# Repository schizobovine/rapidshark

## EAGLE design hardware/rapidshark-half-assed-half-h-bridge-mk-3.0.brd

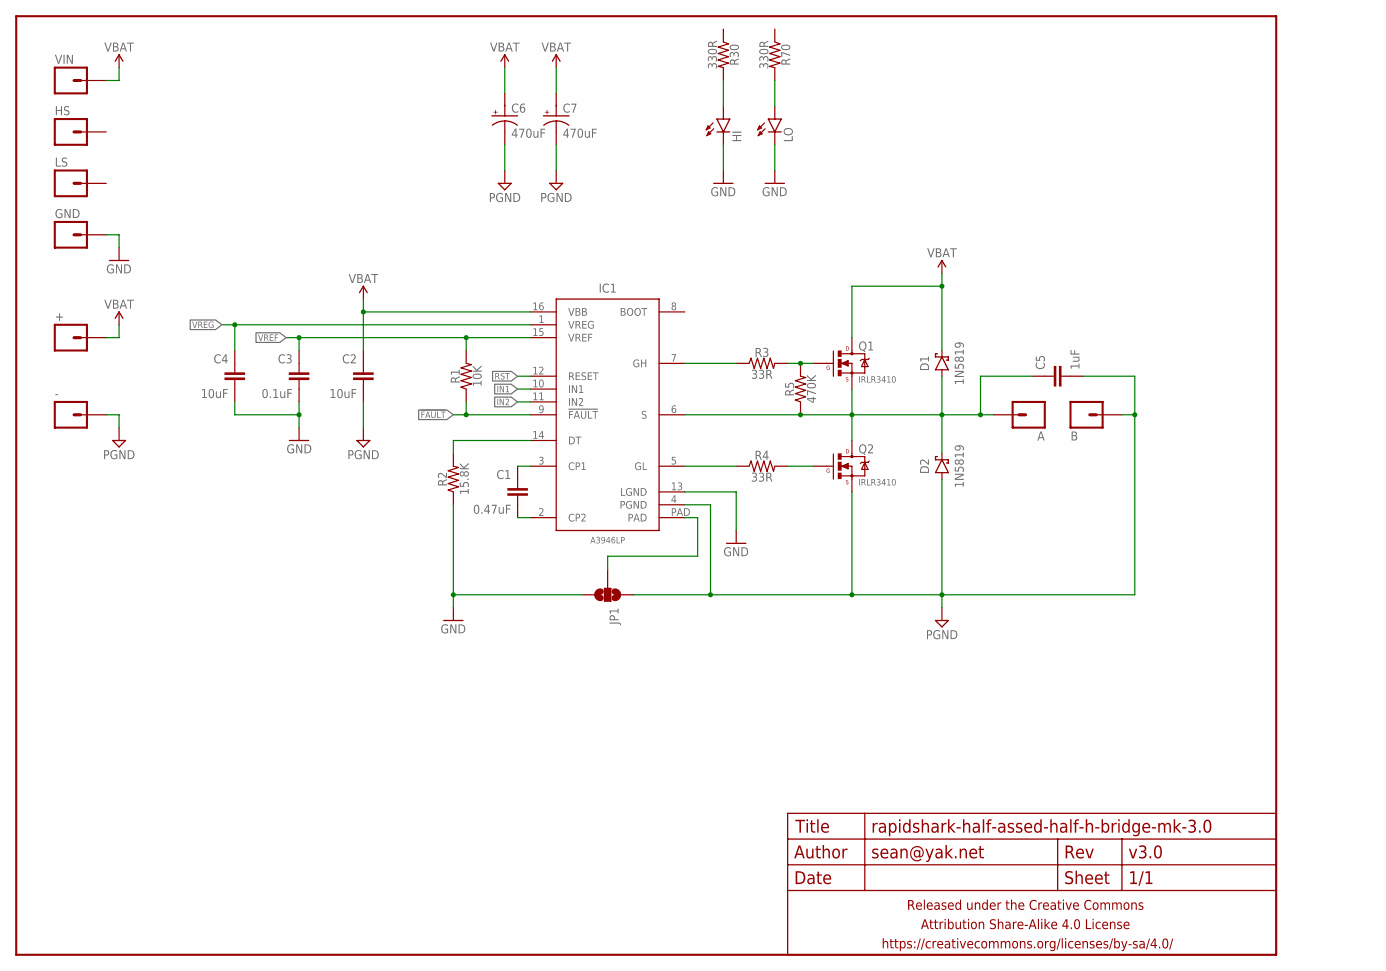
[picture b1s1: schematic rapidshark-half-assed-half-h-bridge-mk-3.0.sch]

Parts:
+: M01PTH-1.9MM; 1X01-1.9MM-CIR
-: M01PTH-1.9MM; 1X01-1.9MM-CIR
A: M01PTH-1.9MM; 1X01-1.9MM-CIR
B: M01PTH-1.9MM; 1X01-1.9MM-CIR
C1: 0.47uF; C0603-TIGHTER
C2, C4: 10uF; C0805-TIGHTER
C3: 0.1uF; C0603-TIGHTER
C5: 1uF; C0603-TIGHTER
C6, C7: 470uF; E5-10,5
D1, D2: 1N5819; SMA-DIODE-SCHOTTKY
FRAME1: FRAME-LETTERNO_PACKAGE; DUMMY
GND: M01PTH; 1X01
HI: LED0603-TIGHT; LED-0603-TIGHT
HS: M01PTH; 1X01
IC1: A3946LP; TSSOP-16-PAD
JP1: JUMPER-PAD-3-NOFULL_BOX_SILK; PAD-JUMPER-3-NO_YES_SILK_FULL_BOX
LO: LED0603-TIGHT; LED-0603-TIGHT
LS: M01PTH; 1X01
Q1, Q2: IRLR3410; DPAK
R1: 10K; R0603-TIGHTER
R2: 15.8K; R0603-TIGHTER
R3, R4: 33R; R0603-TIGHTER
R5: 470K; R0603-TIGHTER
R30, R70: 330R; R0603-TIGHTER
VIN: M01PTH; 1X01

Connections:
!FAULT: IC1.9 (!FAULT), R1.1
A: A.P$1, C5.1, D1.A, D2.C, IC1.6 (S), Q1.3 (S), Q2.4 (D), R5.1
GND: C3.2, C4.2, GND.1, HI.C, IC1.13 (LGND), JP1.3, LO.C, R2.1
IN1: IC1.10 (IN1)
IN2: IC1.11 (IN2)
unnamed: Q2.1 (G), R4.2
unnamed: C1.1, IC1.3 (CP1)
unnamed: LO.A, R70.2
unnamed: HI.A, R30.2
unnamed: Q1.1 (G), R3.2, R5.2
unnamed: C1.2, IC1.2 (CP2)
unnamed: IC1.14 (DT), R2.2
unnamed: IC1.PAD, JP1.2
unnamed: IC1.5 (GL), R4.1
unnamed: IC1.7 (GH), R3.1
PGND: -.P$1, B.P$1, C2.2, C5.2, C6.-, C7.-, D2.A, IC1.4 (PGND), JP1.1, Q2.3 (S)
RST: IC1.12 (RESET)
VBAT: +.P$1, C2.1, C6.+, C7.+, D1.C, IC1.16 (VBB), Q1.4 (D), VIN.1
VREF: C3.1, IC1.15 (VREF), R1.2
VREG: C4.1, IC1.1 (VREG)

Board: 2 copper layers, 34 parts (5 on the bottom side), 17 nets, no tracks yet.

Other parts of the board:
U$1: COW
U$2: CC-BY-SA-4.0-NO-URL
U$3: OSHWLOGO_5MM

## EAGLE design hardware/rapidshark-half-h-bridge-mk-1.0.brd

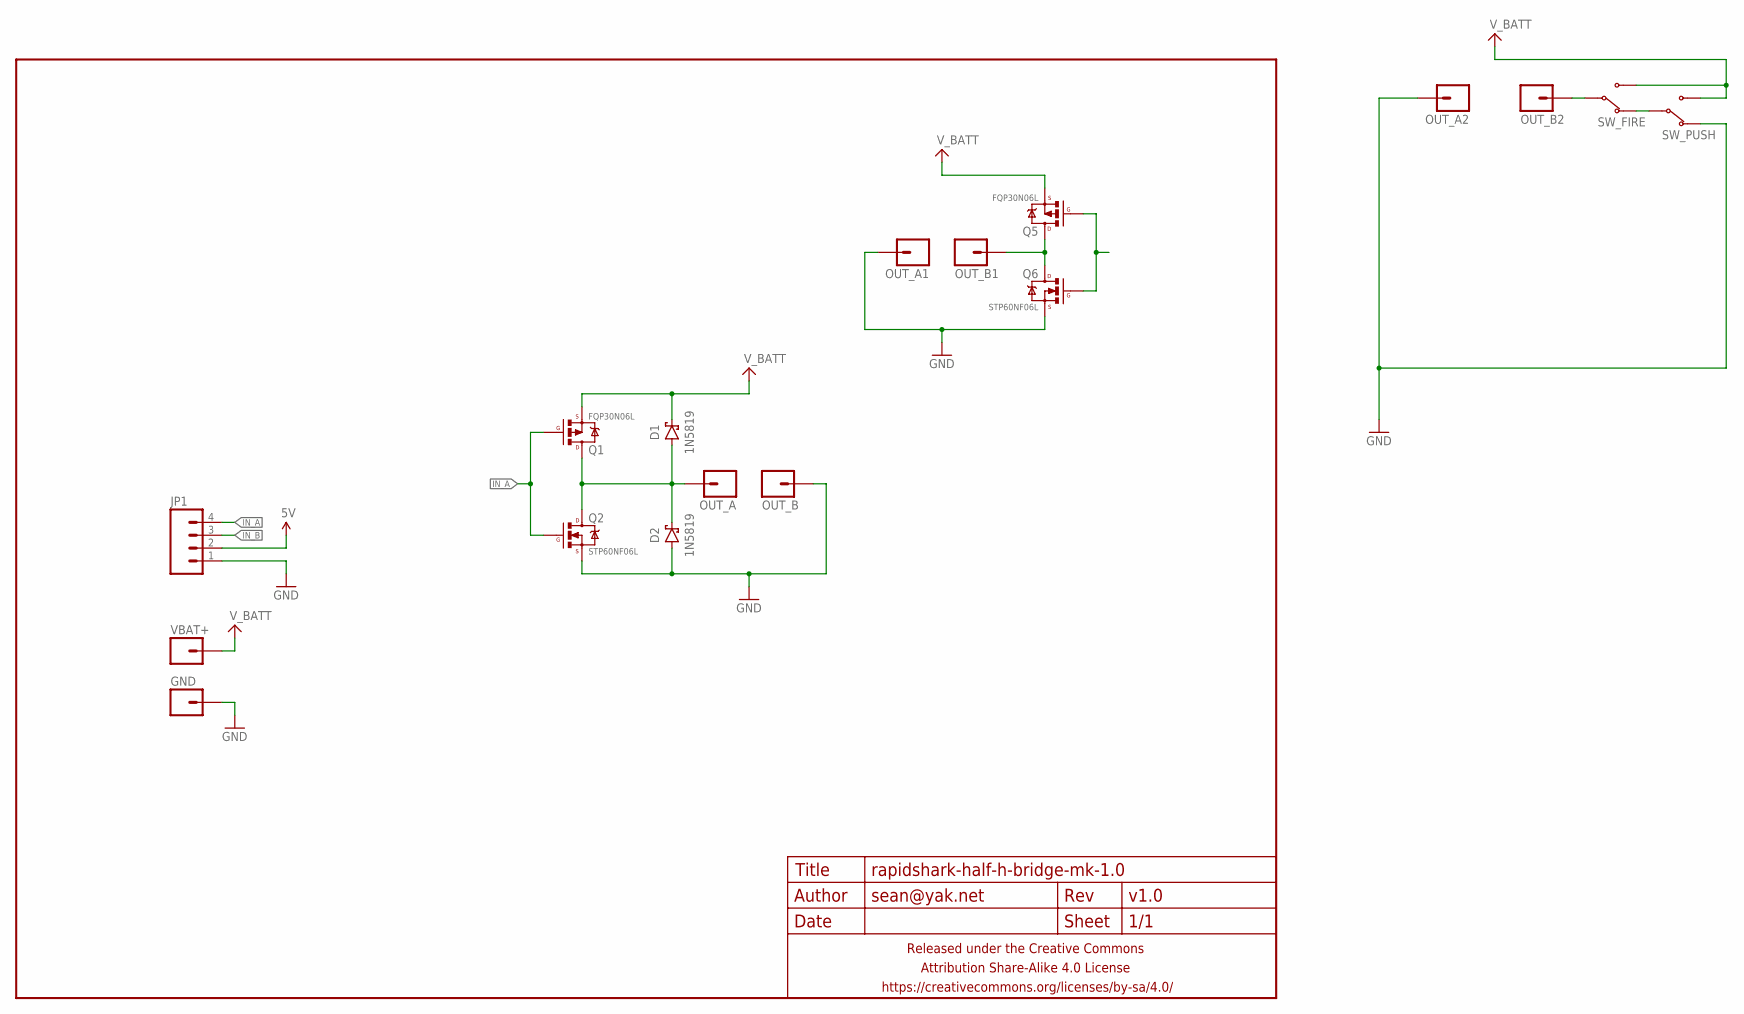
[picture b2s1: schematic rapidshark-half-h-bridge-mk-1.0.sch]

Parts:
D1, D2: 1N5819; DIODE-SCHOTTKY-10.16MM
FRAME1: FRAME-LETTERNO_PACKAGE; DUMMY
GND: M0112AWG; 1X01-12AWG
JP1: M04PTH; 1X04-PTH-VERT
OUT_A, OUT_A1, OUT_A2: M0112AWG; 1X01-12AWG
OUT_B, OUT_B1, OUT_B2: M0112AWG; 1X01-12AWG
Q1, Q5: FQP30N06L; TO220-THERMPAD
Q2, Q6: STP60NF06L; TO220-THERMPAD
SW_FIRE: SWITCH-SPDTPTH-VERT-2.54MM; SWITCH-SPDT
SW_PUSH: SWITCH-SPDTPTH-VERT-2.54MM; SWITCH-SPDT
VBAT+: M0112AWG; 1X01-12AWG

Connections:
5V: JP1.2
A: D1.A, D2.C, OUT_A.1, Q1.2@1 (D), Q1.2@2 (D), Q2.2@1 (D), Q2.2@2 (D)
GND: D2.A, GND.1, JP1.1, OUT_A1.1, OUT_A2.1, OUT_B.1, Q2.3 (S), Q6.3 (S), SW_PUSH.1 (NC)
IN_A: JP1.4, Q1.1 (G), Q2.1 (G)
IN_B: JP1.3
unnamed: OUT_B1.1, Q5.2@1 (D), Q5.2@2 (D), Q6.2@1 (D), Q6.2@2 (D)
unnamed: SW_FIRE.1 (NC), SW_PUSH.2 (COM)
unnamed: OUT_B2.1, SW_FIRE.2 (COM)
unnamed: Q5.1 (G), Q6.1 (G)
V_BATT: D1.C, Q1.3 (S), Q5.3 (S), SW_FIRE.3 (NO), SW_PUSH.3 (NO), VBAT+.1

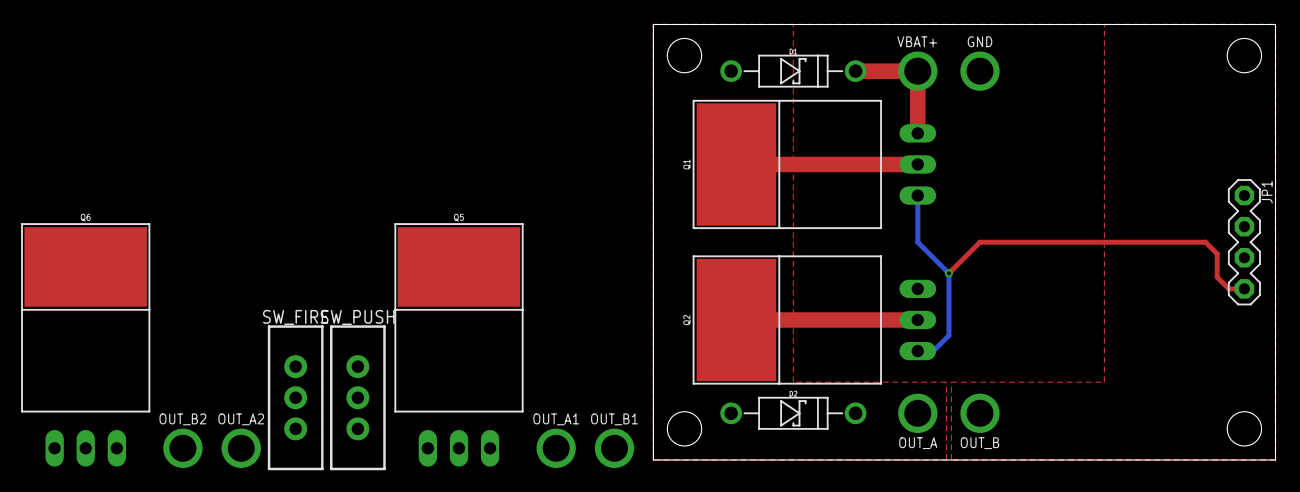
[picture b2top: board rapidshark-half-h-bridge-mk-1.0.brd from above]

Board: 2 copper layers, 50.8 x 35.6 mm, 18 parts (1 on the bottom side), 8 nets.

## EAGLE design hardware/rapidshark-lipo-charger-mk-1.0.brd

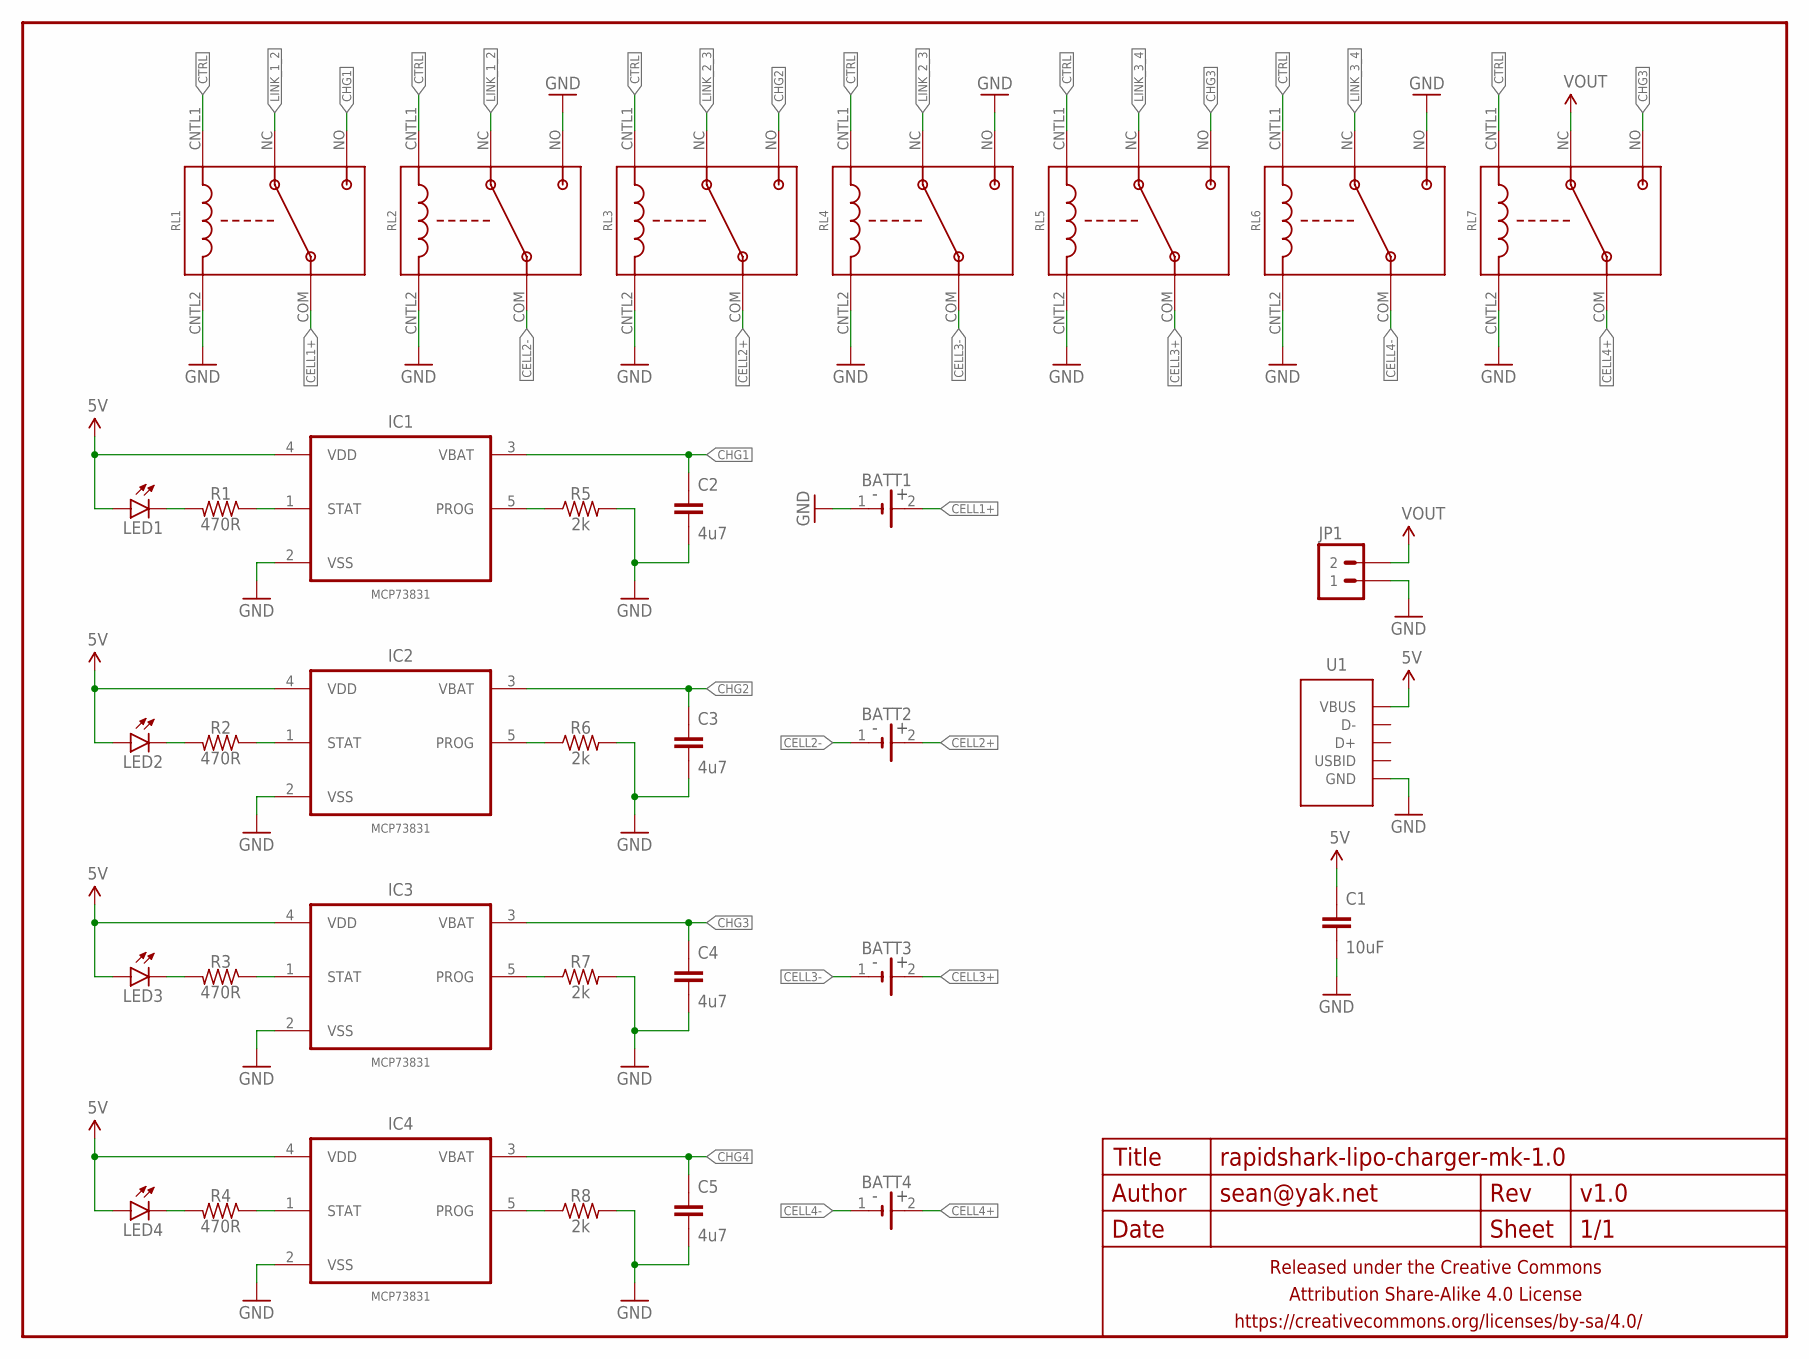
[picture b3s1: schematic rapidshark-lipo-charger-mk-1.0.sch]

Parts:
BATT1, BATT2, BATT3, BATT4: LIPO1S_3.7V_EXT0.1IN_PTH; 1X02-CENTER-R+
C1: 10uF; C0805
C2, C3, C4, C5: 4u7; C0805
FRAME1: FRAME-LETTERNO_PACKAGE; DUMMY
IC1, IC2, IC3, IC4: MCP73831; SOT95P280X145-5N
JP1: M025MM; SCREWTERMINAL-5MM-2
LED1, LED2, LED3, LED4: LED0805; LED-0805
R1, R2, R3, R4: 470R; R0805
R5, R6, R7, R8: 2k; R0805
RL1, RL2, RL3, RL4, RL5, RL6, RL7: RELAY-SPDTMC25131; RELAY-SPDT-MC25131
U1: USB-ABFCI-10103594-USB-MICRO-B-LESS; FCI-10103594-USB-MICRO-B-LESS

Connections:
5V: C1.1, IC1.4 (VDD), IC2.4 (VDD), IC3.4 (VDD), IC4.4 (VDD), LED1.A, LED2.A, LED3.A, LED4.A, U1.1 (VBUS)
CELL1+: BATT1.2 (+), RL1.COM
CELL2+: BATT2.2 (+), RL3.COM
CELL2-: BATT2.1 (-), RL2.COM
CELL3+: BATT3.2 (+), RL5.COM
CELL3-: BATT3.1 (-), RL4.COM
CELL4+: BATT4.2 (+), RL7.COM
CELL4-: BATT4.1 (-), RL6.COM
CHG1: C2.1, IC1.3 (VBAT), RL1.NO
CHG2: C3.1, IC2.3 (VBAT), RL3.NO
CHG3: C4.1, IC3.3 (VBAT), RL5.NO, RL7.NO
CHG4: C5.1, IC4.3 (VBAT)
CTRL: RL1.CNTL1, RL2.CNTL1, RL3.CNTL1, RL4.CNTL1, RL5.CNTL1, RL6.CNTL1, RL7.CNTL1
GND: BATT1.1 (-), C1.2, C2.2, C3.2, C4.2, C5.2, IC1.2 (VSS), IC2.2 (VSS), IC3.2 (VSS), IC4.2 (VSS), JP1.1, R5.2, R6.2, R7.2, R8.2, RL1.CNTL2, RL2.CNTL2, RL2.NO, RL3.CNTL2, RL4.CNTL2, RL4.NO, RL5.CNTL2, RL6.CNTL2, RL6.NO, RL7.CNTL2, U1.5 (GND)
LINK_1_2: RL1.NC, RL2.NC
LINK_2_3: RL3.NC, RL4.NC
LINK_3_4: RL5.NC, RL6.NC
unnamed: LED1.C, R1.2
unnamed: IC1.1 (STAT), R1.1
unnamed: LED2.C, R2.2
unnamed: LED3.C, R3.2
unnamed: LED4.C, R4.2
unnamed: IC2.1 (STAT), R2.1
unnamed: IC3.1 (STAT), R3.1
unnamed: IC4.1 (STAT), R4.1
unnamed: IC1.5 (PROG), R5.1
unnamed: IC2.5 (PROG), R6.1
unnamed: IC3.5 (PROG), R7.1
unnamed: IC4.5 (PROG), R8.1
VOUT: JP1.2, RL7.NC

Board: 2 copper layers, 35 parts (0 on the bottom side), 30 nets, no tracks yet.

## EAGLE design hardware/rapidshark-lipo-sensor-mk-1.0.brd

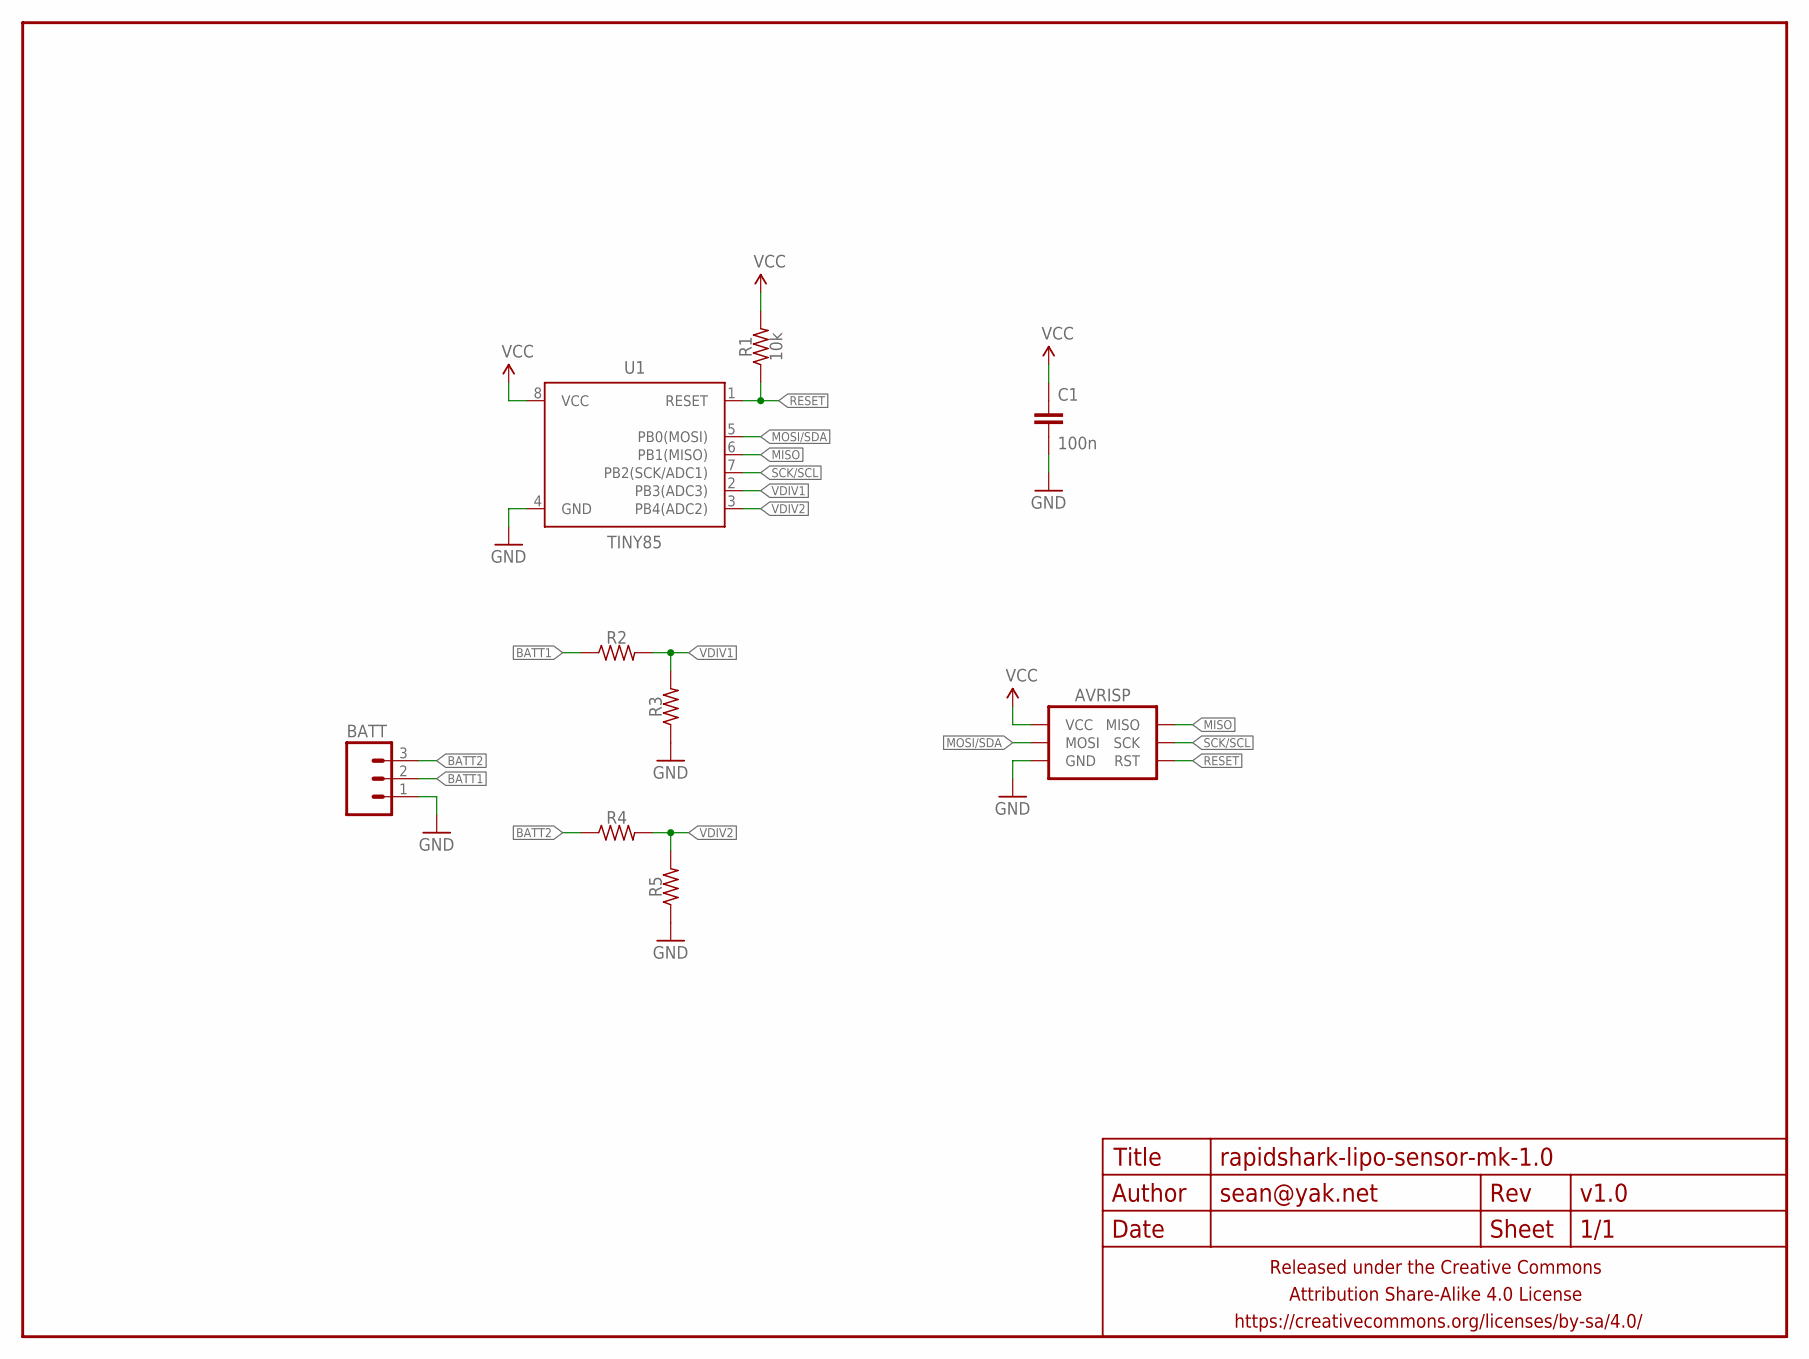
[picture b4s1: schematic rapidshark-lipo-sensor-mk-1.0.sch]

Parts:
AVRISP: AVR_SPI_PRG_6PTH_INLINE_I2C; AVR_ISP_INLINE_PTH_I2C
BATT: M03PTH-CENTERED; 1X03-CENTERED
C1: 100n; C025-024X044
FRAME1: FRAME-LETTERNO_PACKAGE; DUMMY
R1: 10k; RESISTOR-AXIAL-PTH-7.62MM
R2, R3, R4, R5: RESISTORPTH-AXIAL-7.62MM; RESISTOR-AXIAL-PTH-7.62MM
U1: TINY85; DIP08

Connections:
BATT1: BATT.2, R2.P$1 (1)
BATT2: BATT.3, R4.P$1 (1)
GND: AVRISP.GND, BATT.1, C1.2, R3.P$1 (1), R5.P$1 (1), U1.4 (GND)
MISO: AVRISP.MISO, U1.6 (PB1(MISO))
MOSI/SDA: AVRISP.MOSI, U1.5 (PB0(MOSI))
RESET: AVRISP.RESET (RST), R1.P$1 (1), U1.1 (RESET)
SCK/SCL: AVRISP.SCK, U1.7 (PB2(SCK/ADC1))
VCC: AVRISP.VCC, C1.1, R1.P$2 (2), U1.8 (VCC)
VDIV1: R2.P$2 (2), R3.P$2 (2), U1.2 (PB3(ADC3))
VDIV2: R4.P$2 (2), R5.P$2 (2), U1.3 (PB4(ADC2))

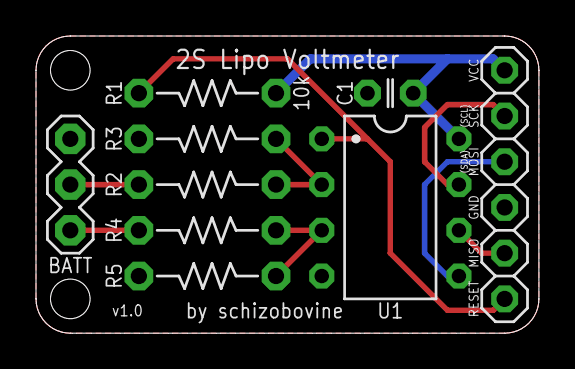
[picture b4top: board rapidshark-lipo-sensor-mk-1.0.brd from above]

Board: 2 copper layers, 27.9 x 16.5 mm, 10 parts (0 on the bottom side), 10 nets.

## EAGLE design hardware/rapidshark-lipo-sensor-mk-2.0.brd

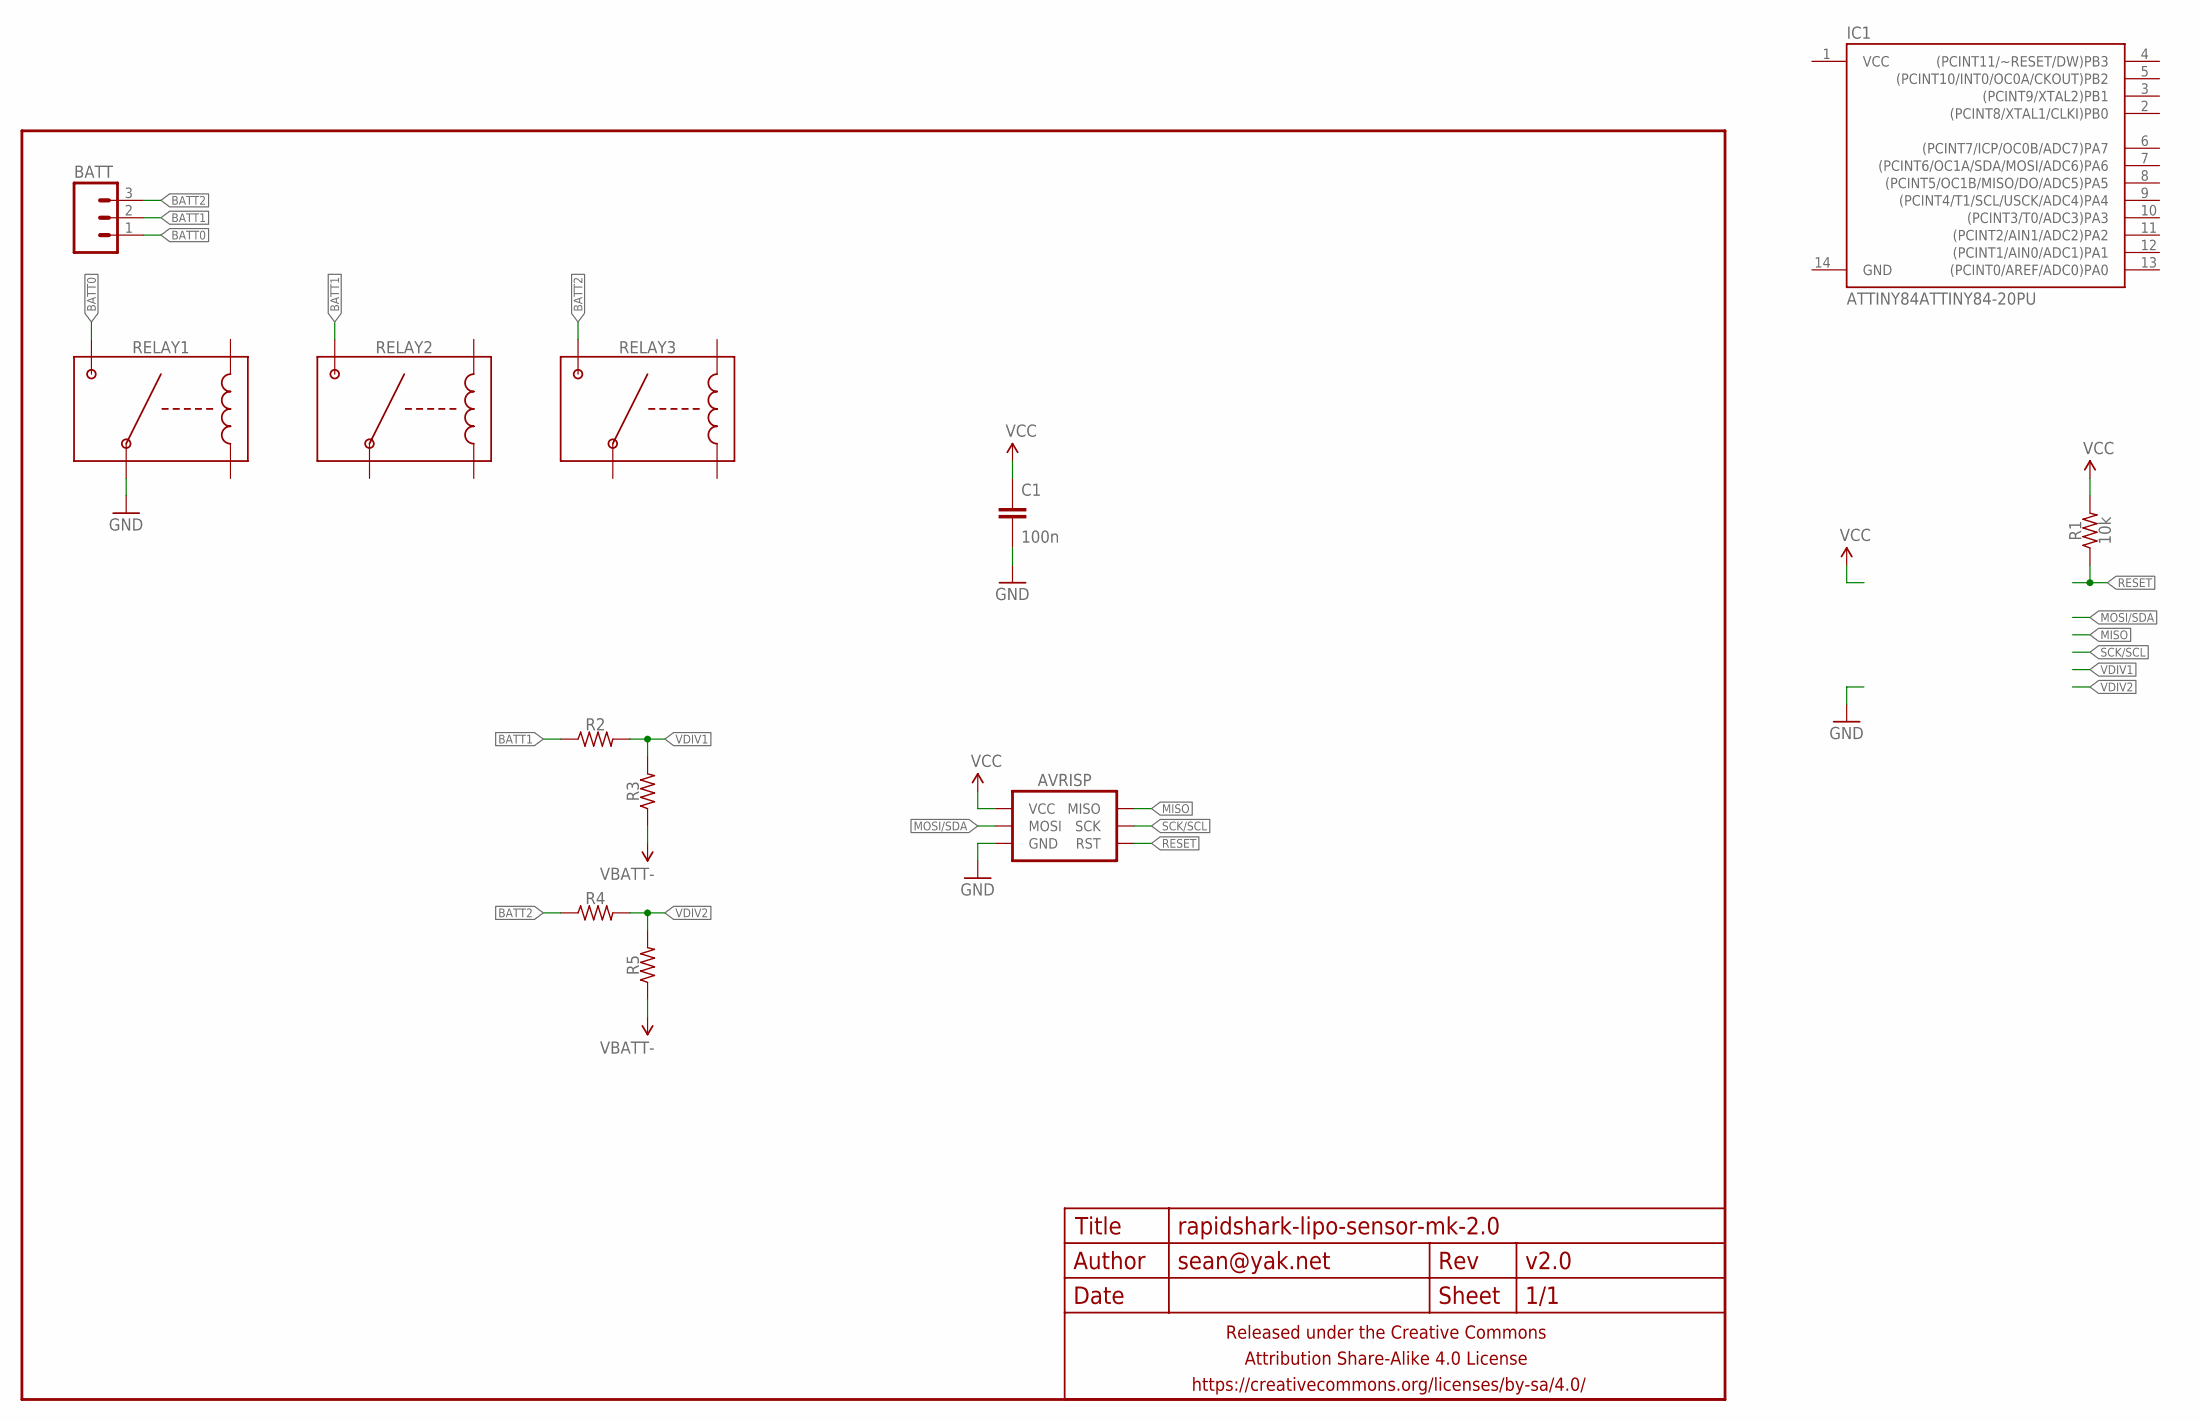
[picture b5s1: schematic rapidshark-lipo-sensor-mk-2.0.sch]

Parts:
AVRISP: AVR_SPI_PRG_6PTH_INLINE_I2C; AVR_ISP_INLINE_PTH_I2C
BATT: M03PTH-CENTERED; 1X03-CENTERED
C1: 100n; C025-024X044
FRAME1: FRAME-LETTERNO_PACKAGE; DUMMY
IC1: ATTINY84ATTINY84-20PU; DIL14
R1: 10k; RESISTOR-AXIAL-PTH-7.62MM
R2, R3, R4, R5: RESISTORPTH-AXIAL-7.62MM; RESISTOR-AXIAL-PTH-7.62MM
RELAY1, RELAY2, RELAY3: RELAY-SPST-NOCOTO-9007; RELAY-SPST-NO-COTO-9007

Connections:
BATT0: BATT.1, RELAY1.4 (NO)
BATT1: BATT.2, R2.P$1 (1), RELAY2.4 (NO)
BATT2: BATT.3, R4.P$1 (1), RELAY3.4 (NO)
GND: AVRISP.GND, C1.2, RELAY1.1 (COM)
MISO: AVRISP.MISO
MOSI/SDA: AVRISP.MOSI
RESET: AVRISP.RESET (RST), R1.P$1 (1)
SCK/SCL: AVRISP.SCK
VBATT-: R3.P$1 (1), R5.P$1 (1)
VCC: AVRISP.VCC, C1.1, R1.P$2 (2)
VDIV1: R2.P$2 (2), R3.P$2 (2)
VDIV2: R4.P$2 (2), R5.P$2 (2)

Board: 2 copper layers, 13 parts (0 on the bottom side), 9 nets, no tracks yet.

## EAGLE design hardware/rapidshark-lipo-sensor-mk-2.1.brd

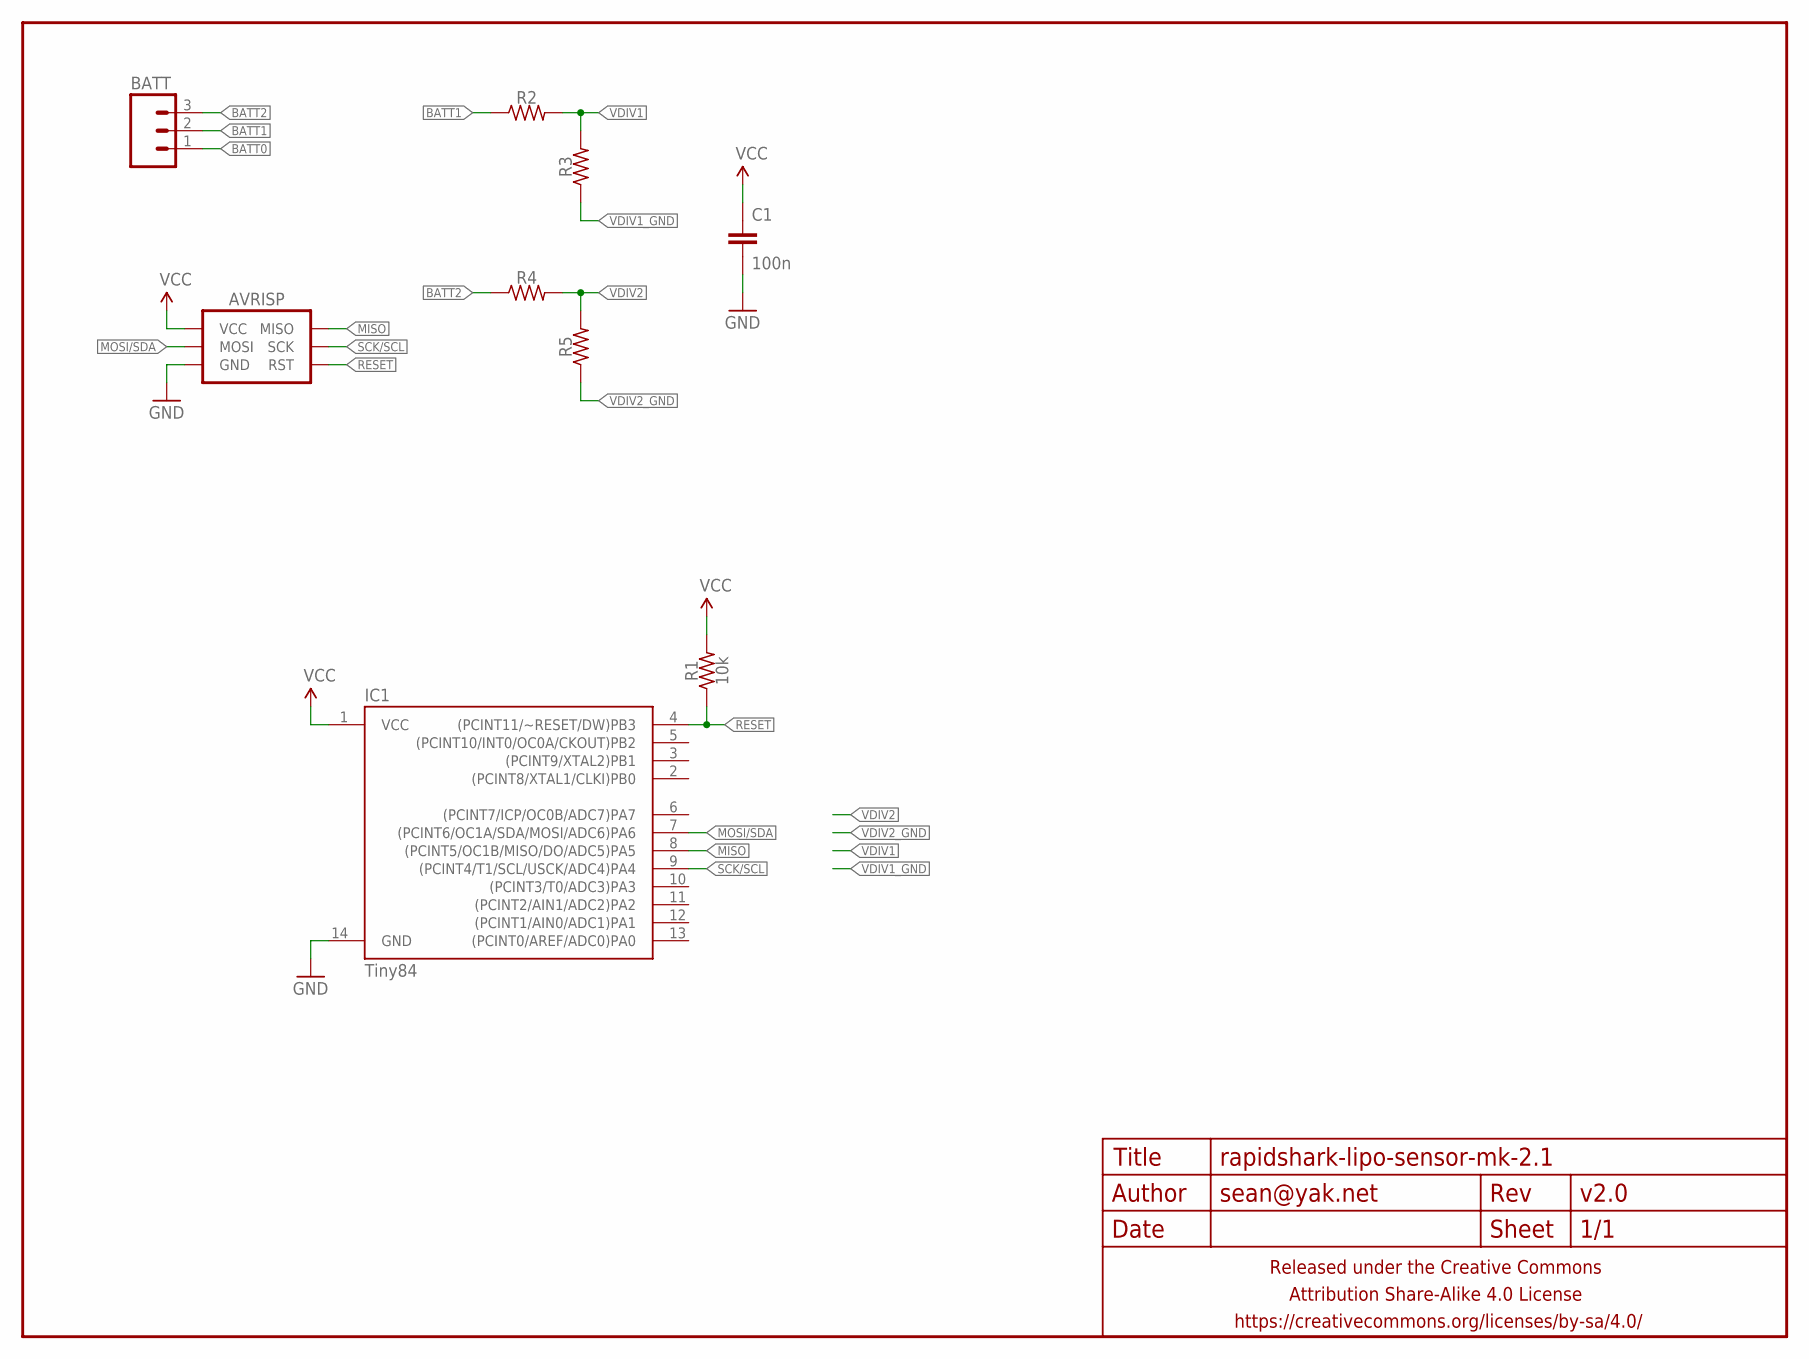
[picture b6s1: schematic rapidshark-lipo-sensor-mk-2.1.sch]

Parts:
AVRISP: AVR_SPI_PRG_6PTH_INLINE_I2C; AVR_ISP_INLINE_PTH_I2C
BATT: M03PTH-CENTERED; 1X03-CENTERED
C1: 100n; C025-024X044
FRAME1: FRAME-LETTERNO_PACKAGE; DUMMY
IC1: Tiny84; DIL14
R1: 10k; RESISTOR-AXIAL-PTH-5.08MM
R2, R3, R4, R5: RESISTORPTH-AXIAL-5.08MM; RESISTOR-AXIAL-PTH-5.08MM

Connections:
BATT0: BATT.1
BATT1: BATT.2, R2.P$1 (1)
BATT2: BATT.3, R4.P$1 (1)
GND: AVRISP.GND, C1.2, IC1.14 (GND)
MISO: AVRISP.MISO, IC1.8 ((PCINT5/OC1B/MISO/DO/ADC5)PA5)
MOSI/SDA: AVRISP.MOSI, IC1.7 ((PCINT6/OC1A/SDA/MOSI/ADC6)PA6)
RESET: AVRISP.RESET (RST), IC1.4 ((PCINT11/~RESET/DW)PB3), R1.P$1 (1)
SCK/SCL: AVRISP.SCK, IC1.9 ((PCINT4/T1/SCL/USCK/ADC4)PA4)
VCC: AVRISP.VCC, C1.1, IC1.1 (VCC), R1.P$2 (2)
VDIV1: R2.P$2 (2), R3.P$2 (2)
VDIV1_GND: R3.P$1 (1)
VDIV2: R4.P$2 (2), R5.P$2 (2)
VDIV2_GND: R5.P$1 (1)

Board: 2 copper layers, 10 parts (0 on the bottom side), 10 nets, no tracks yet.

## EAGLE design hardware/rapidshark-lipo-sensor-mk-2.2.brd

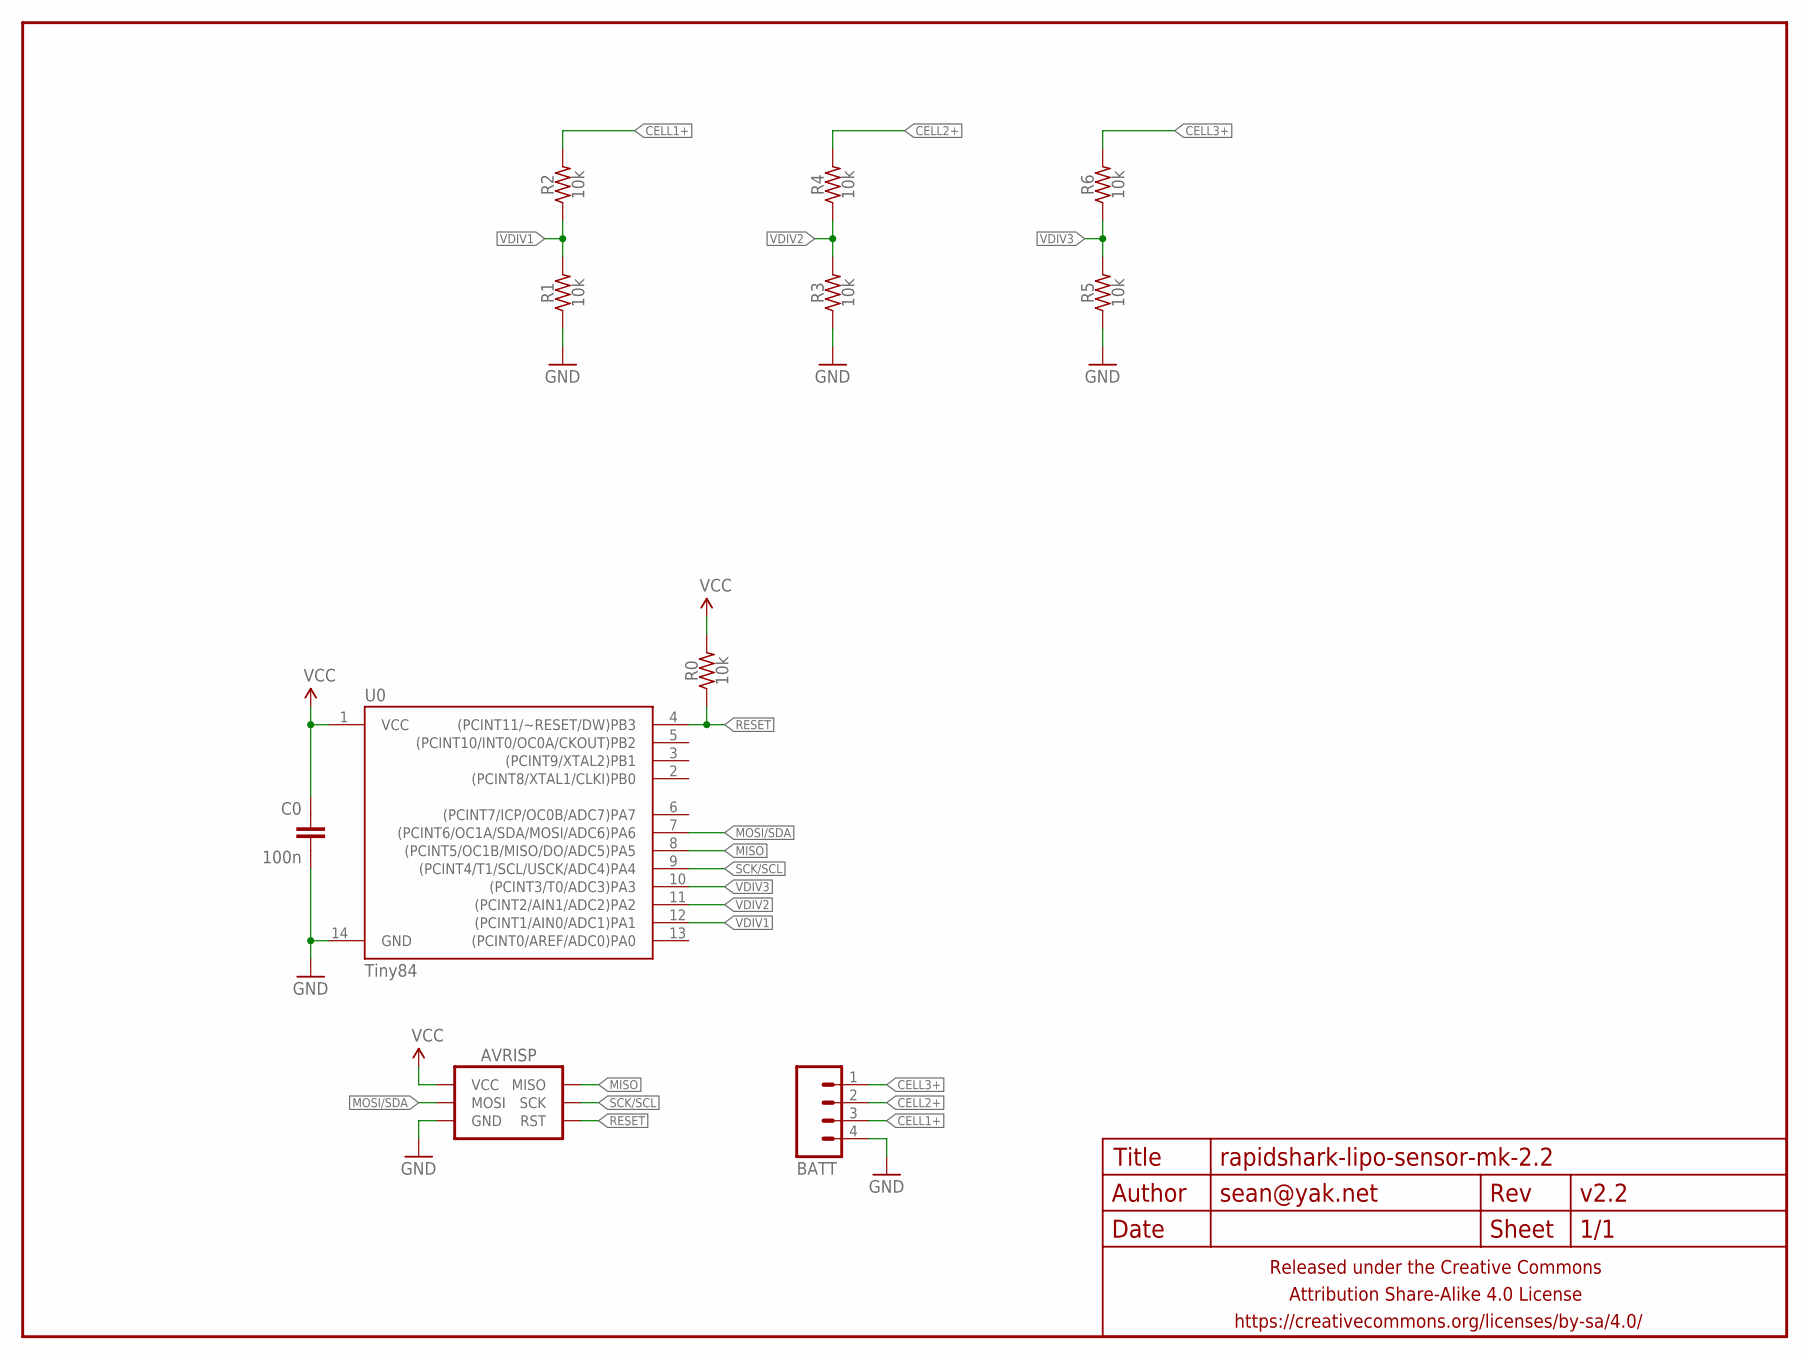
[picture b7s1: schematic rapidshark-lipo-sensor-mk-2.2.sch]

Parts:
AVRISP: AVR_SPI_PRG_6PTH_INLINE_I2C; AVR_ISP_INLINE_PTH_I2C
BATT: M04JST_XH_VERT; JST-4-XH-VERT-TH
C0: 100n; C025-024X044
FRAME1: FRAME-LETTERNO_PACKAGE; DUMMY
R0, R1, R2, R3, R4, R5, R6: 10k; RESISTOR-AXIAL-PTH-5.08MM
U0: Tiny84; DIL14

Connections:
CELL1+: BATT.3, R2.P$2 (2)
CELL2+: BATT.2, R4.P$2 (2)
CELL3+: BATT.1, R6.P$2 (2)
GND: AVRISP.GND, BATT.4, C0.2, R1.P$1 (1), R3.P$1 (1), R5.P$1 (1), U0.14 (GND)
MISO: AVRISP.MISO, U0.8 ((PCINT5/OC1B/MISO/DO/ADC5)PA5)
MOSI/SDA: AVRISP.MOSI, U0.7 ((PCINT6/OC1A/SDA/MOSI/ADC6)PA6)
RESET: AVRISP.RESET (RST), R0.P$1 (1), U0.4 ((PCINT11/~RESET/DW)PB3)
SCK/SCL: AVRISP.SCK, U0.9 ((PCINT4/T1/SCL/USCK/ADC4)PA4)
VCC: AVRISP.VCC, C0.1, R0.P$2 (2), U0.1 (VCC)
VDIV1: R1.P$2 (2), R2.P$1 (1), U0.12 ((PCINT1/AIN0/ADC1)PA1)
VDIV2: R3.P$2 (2), R4.P$1 (1), U0.11 ((PCINT2/AIN1/ADC2)PA2)
VDIV3: R5.P$2 (2), R6.P$1 (1), U0.10 ((PCINT3/T0/ADC3)PA3)

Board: 2 copper layers, 12 parts (0 on the bottom side), 12 nets, no tracks yet.

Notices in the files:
parts and their libraries:
A_butts: Released under the Creative Commons Attribution Share-Alike 4.0 License
A_butts: https://creativecommons.org/licenses/by-sa/4.0
A_butts: Released under the Creative Commons
